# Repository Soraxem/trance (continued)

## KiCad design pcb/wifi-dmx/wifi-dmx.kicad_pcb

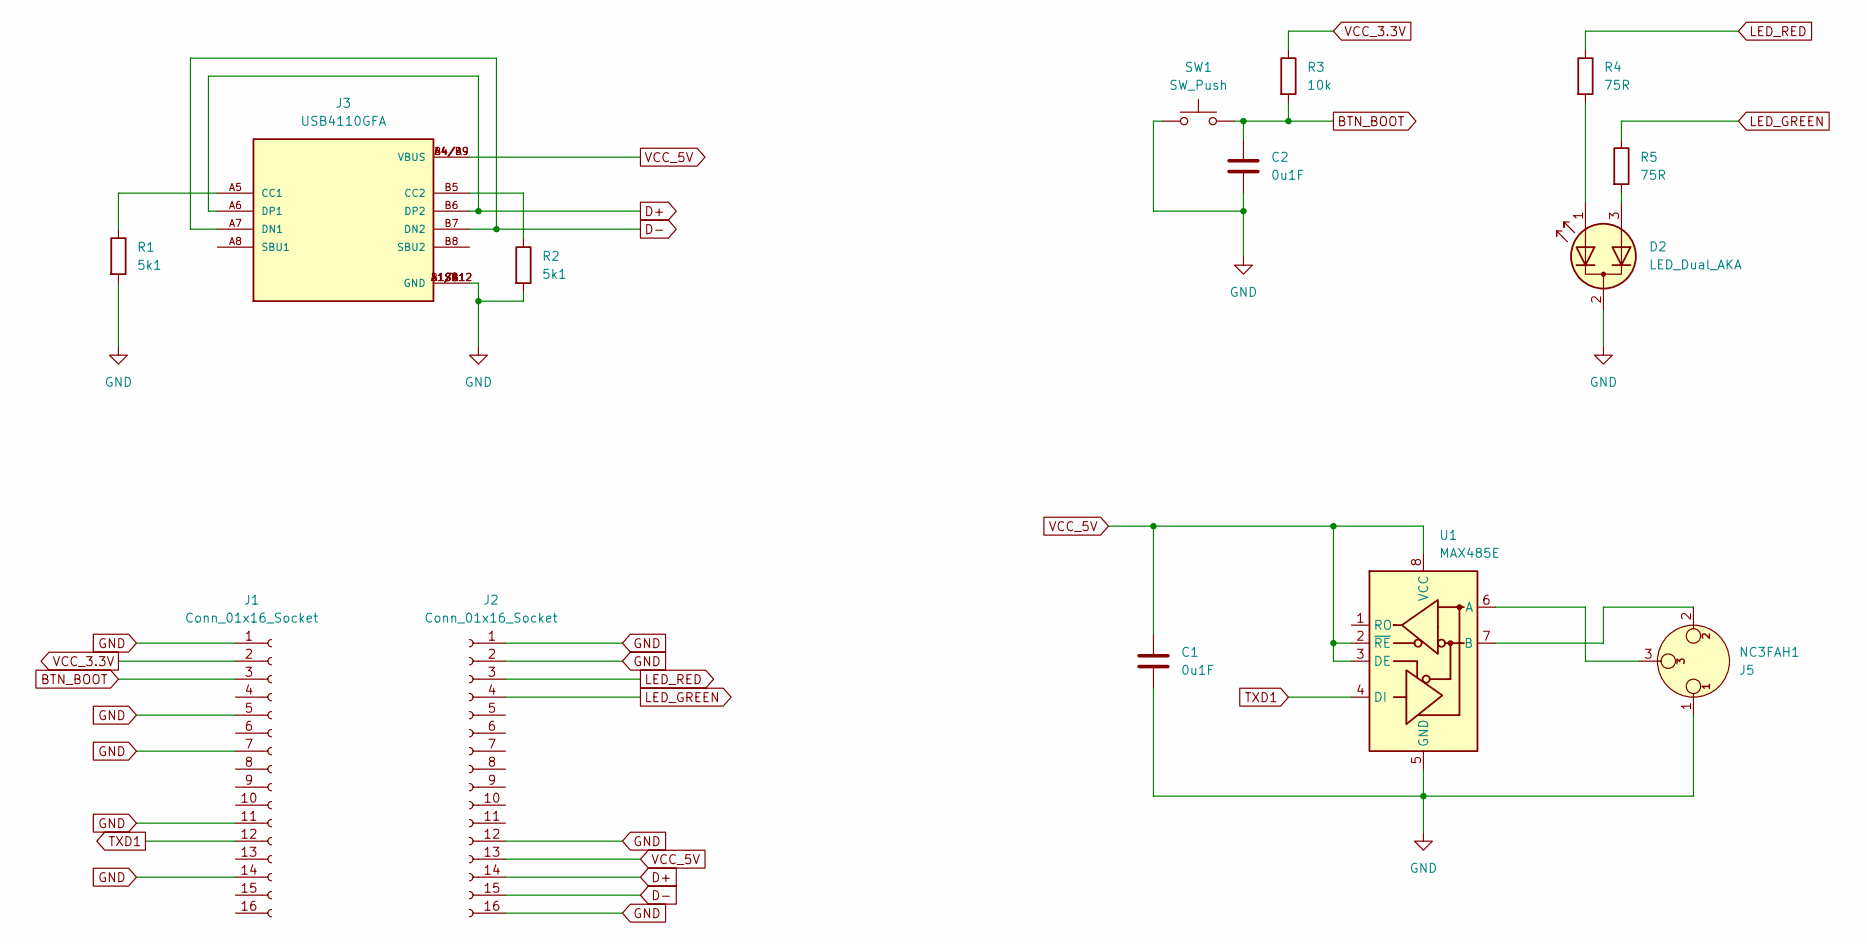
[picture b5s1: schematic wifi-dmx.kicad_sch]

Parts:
C1, C2: 0u1F; C_0402_1005Metric_Pad0.74x0.62mm_HandSolder; MOUSER_PART_NUMBER 187-CL05F104ZO5NNND
D2: LED_Dual_AKA; LED_D5.0mm-3_Horizontal_O3.81mm_Z3.0mm
J1, J2: Conn_01x16_Socket; PinHeader_1x16_P2.54mm_Vertical; MOUSER_PART_NUMBER 200-SSW11601TS
J3: USB4110GFA; GCT_USB4110GFA; MOUSER_PART_NUMBER 640-USB4110-GF-A; DigiKey_Part_Number 2073-USB4110-GF-A-2-ND
J5: NC3FAH1; Jack_XLR_Neutrik_NC3FAH1_Horizontal
R1, R2: 5k1; R_0402_1005Metric_Pad0.72x0.64mm_HandSolder; MOUSER_PART_NUMBER 71-CRCW0402-5.1K-E3
R3: 10k; R_0402_1005Metric_Pad0.72x0.64mm_HandSolder; MOUSER_PART_NUMBER 71-CRCW0402-10K-E3
R4, R5: 75R; R_0402_1005Metric_Pad0.72x0.64mm_HandSolder; MOUSER_PART_NUMBER 71-CRCW040275R0JNEDC
SW1: SW_Push; SW_Tactile_SPST_Angled_PTS645Vx58-2LFS
U1: MAX485E; SOIC-8_3.9x4.9mm_P1.27mm

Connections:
BTN_BOOT: C2.1, J1.3, R3.2, SW1.2
D+: J2.14, J3.A6 (DP1), J3.B6 (DP2)
D-: J2.15, J3.A7 (DN1), J3.B7 (DN2)
GND: C1.2, C2.2, D2.2 (K), J1.1, J1.5, J1.7, J1.11, J1.14, J2.1, J2.2, J2.12, J2.16, J3.A1/B12 (GND), J3.B1/A12 (GND), J3.S1 (GND), J3.S2 (GND), J3.S3 (GND), J3.S4 (GND), J5.1, R1.2, R2.2, SW1.1, U1.5 (GND)
LED_GREEN: J2.4, R5.1
LED_RED: J2.3, R4.1
unnamed: D2.1 (A1), R4.2
unnamed: D2.3 (A2), R5.2
unnamed: J3.A5 (CC1), R1.1
unnamed: J3.B5 (CC2), R2.1
unnamed: J5.3, U1.6 (A)
unnamed: J5.2, U1.7 (B)
TXD1: J1.12, U1.4 (DI)
VCC_3.3V: J1.2, R3.1
VCC_5V: C1.1, J2.13, J3.A4/B9 (VBUS), J3.B4/A9 (VBUS), U1.2 (~RE), U1.3 (DE), U1.8 (VCC)

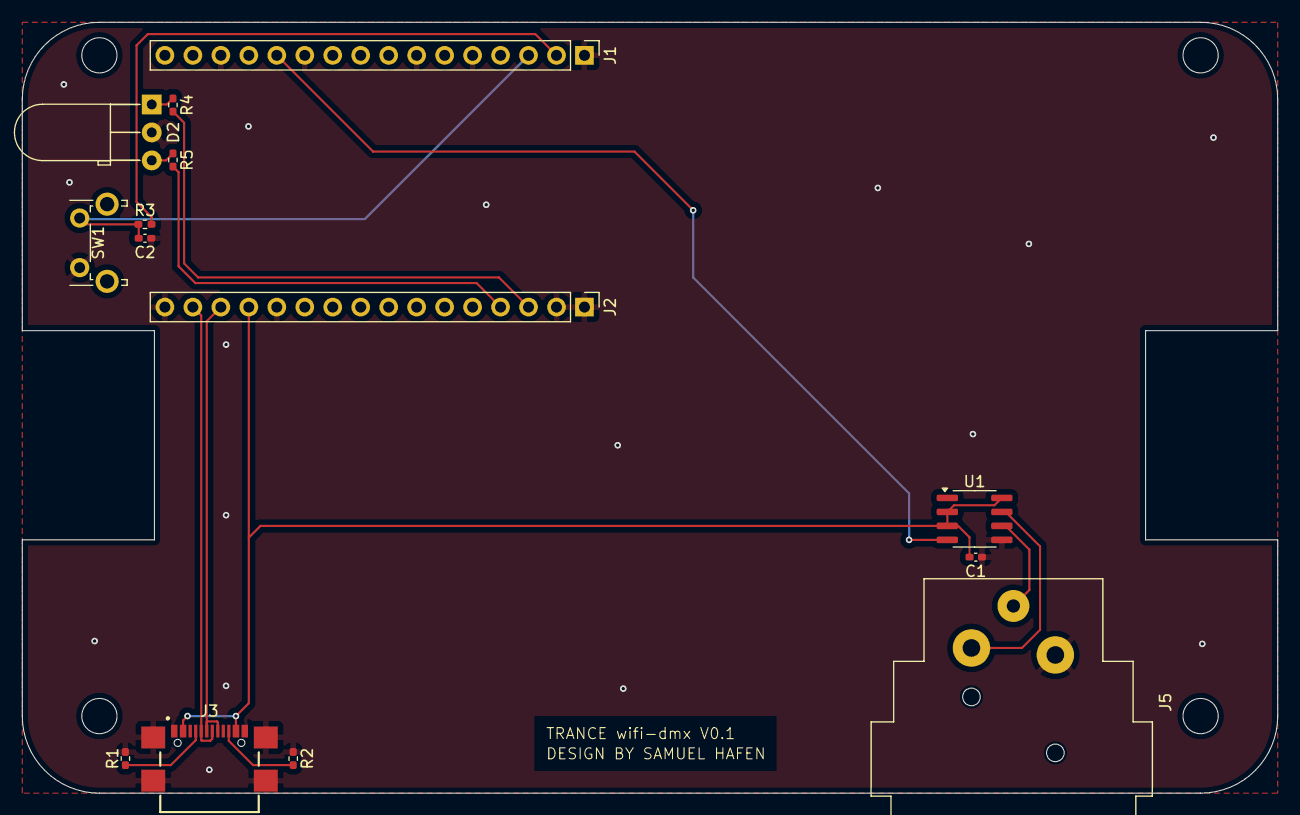
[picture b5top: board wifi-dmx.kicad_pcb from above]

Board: 2 copper layers, 114.0 x 70.0 mm, 14 parts (0 on the bottom side), 15 nets.

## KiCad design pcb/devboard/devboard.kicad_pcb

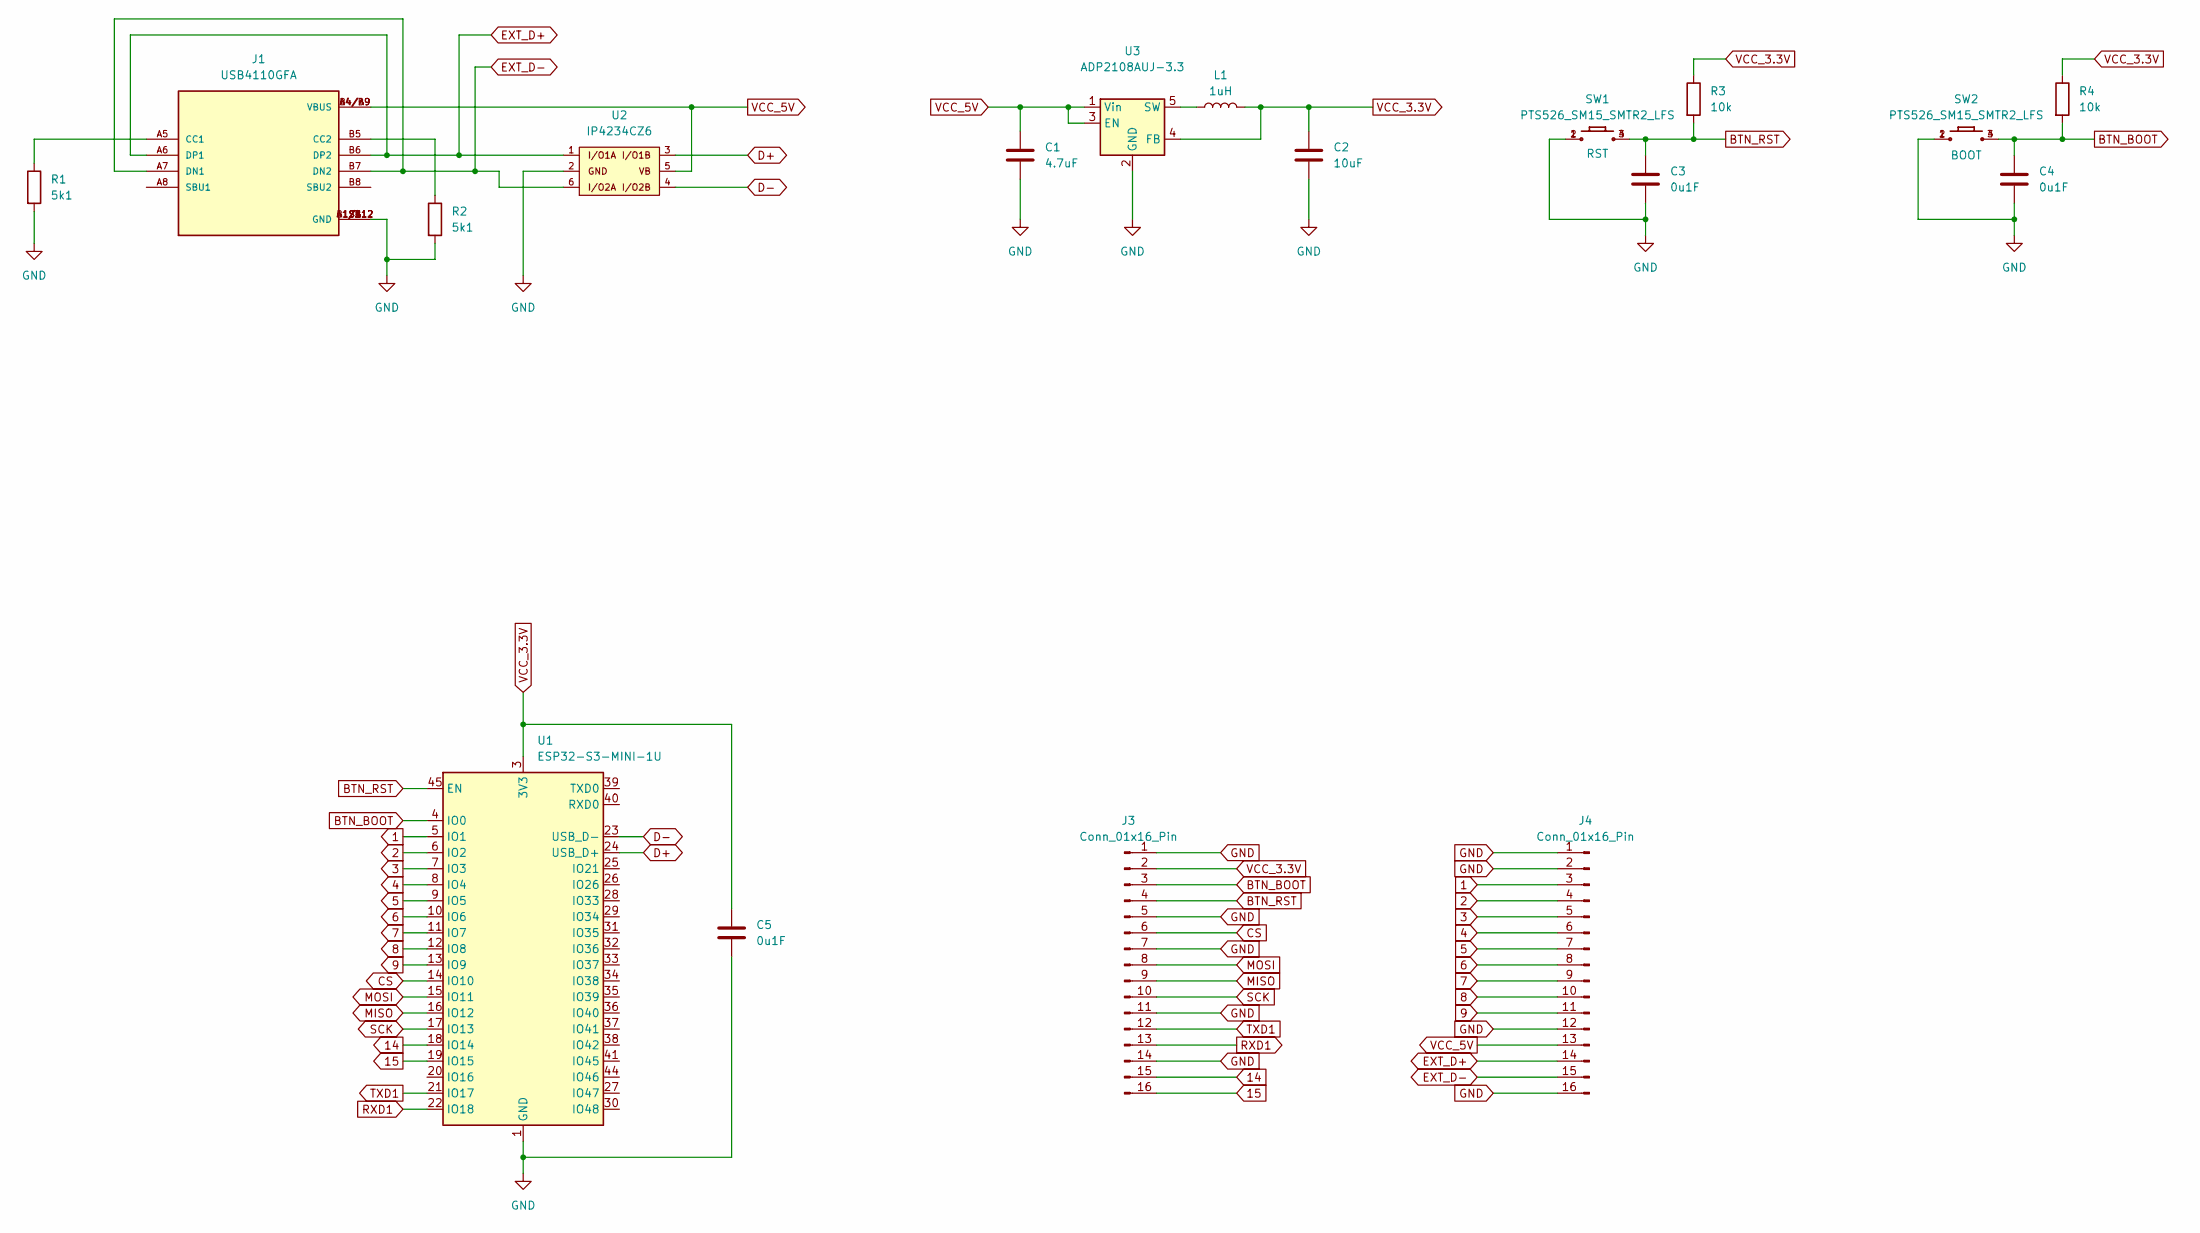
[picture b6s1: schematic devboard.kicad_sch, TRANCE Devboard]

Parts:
C1: 4.7uF; C_0603_1608Metric; MOUSER_PART_NUMBER 187-CL10A475KO8NNNC
C2: 10uF; C_0805_2012Metric; MOUSER_PART_NUMBER 187-CL21A106KOQNNNF
C3, C4, C5: 0u1F; C_0402_1005Metric; MOUSER_PART_NUMBER 187-CL05F104ZO5NNND
J1: USB4110GFA; GCT_USB4110GFA; MOUSER_PART_NUMBER 640-USB4110-GF-A; DigiKey_Part_Number 2073-USB4110-GF-A-2-ND
J3, J4: Conn_01x16_Pin; PinHeader_1x16_P2.54mm_Vertical; MOUSER_PART_NUMBER 200-TSW11607TS
L1: 1uH; L_0805_2012Metric; MOUSER_PART_NUMBER 81-LQM21PN1R0MC0D
R1, R2: 5k1; R_0402_1005Metric; MOUSER_PART_NUMBER 71-CRCW0402-5.1K-E3
R3, R4: 10k; R_0402_1005Metric; MOUSER_PART_NUMBER 71-CRCW0402-10K-E3
SW1, SW2: PTS526_SM15_SMTR2_LFS; PTS526SM15SMTR2LFS; MOUSER_PART_NUMBER 611-PTS526SM15SMTR2L
U1: ESP32-S3-MINI-1U; ESP32-S2-MINI-1U; MOUSER_PART_NUMBER 356-ESP32S3MINI1UN8
U2: IP4234CZ6; IP4234CZ6_SOT-457-6; MOUSER_PART_NUMBER 771-IP4234CZ6
U3: ADP2108AUJ-3.3; TSOT-23-5; MOUSER_PART_NUMBER 584-ADP2108AUJZ3.3R7

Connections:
1: J4.3, U1.5 (IO1)
2: J4.4, U1.6 (IO2)
3: J4.5, U1.7 (IO3)
4: J4.6, U1.8 (IO4)
5: J4.7, U1.9 (IO5)
6: J4.8, U1.10 (IO6)
7: J4.9, U1.11 (IO7)
8: J4.10, U1.12 (IO8)
9: J4.11, U1.13 (IO9)
14: J3.15, U1.18 (IO14)
15: J3.16, U1.19 (IO15)
BTN_BOOT: C4.1, J3.3, R4.2, SW2.3, SW2.4, U1.4 (IO0)
BTN_RST: C3.1, J3.4, R3.2, SW1.3, SW1.4, U1.45 (EN)
CS: J3.6, U1.14 (IO10)
D+: U1.24 (USB_D+), U2.3
D-: U1.23 (USB_D-), U2.4
EXT_D+: J1.A6 (DP1), J1.B6 (DP2), J4.14, U2.1
EXT_D-: J1.A7 (DN1), J1.B7 (DN2), J4.15, U2.6
GND: C1.2, C2.2, C3.2, C4.2, C5.2, J1.A1/B12 (GND), J1.B1/A12 (GND), J1.S1 (GND), J1.S2 (GND), J1.S3 (GND), J1.S4 (GND), J3.1, J3.5, J3.7, J3.11, J3.14, J4.1, J4.2, J4.12, J4.16, R1.2, R2.2, SW1.1, SW1.2, SW2.1, SW2.2, U1.1 (GND), U1.2 (GND), U1.42 (GND), U1.43 (GND), U1.46 (GND), U1.47 (GND), U1.48 (GND), U1.49 (GND), U1.50 (GND), U1.51 (GND), U1.52 (GND), U1.53 (GND), U1.54 (GND), U1.55 (GND), U1.56 (GND), U1.57 (GND), U1.58 (GND), U1.59 (GND), U1.60 (GND), U1.61 (GND), U1.62 (GND), U1.63 (GND), U1.64 (GND), U1.65 (GND), U2.2, U3.2 (GND)
MISO: J3.9, U1.16 (IO12)
MOSI: J3.8, U1.15 (IO11)
unnamed: J1.A5 (CC1), R1.1
unnamed: J1.B5 (CC2), R2.1
unnamed: L1.1, U3.5 (SW)
RXD1: J3.13, U1.22 (IO18)
SCK: J3.10, U1.17 (IO13)
TXD1: J3.12, U1.21 (IO17)
VCC_3.3V: C2.1, C5.1, J3.2, L1.2, R3.1, R4.1, U1.3 (3V3), U3.4 (FB)
VCC_5V: C1.1, J1.A4/B9 (VBUS), J1.B4/A9 (VBUS), J4.13, U2.5, U3.1 (Vin), U3.3 (EN)

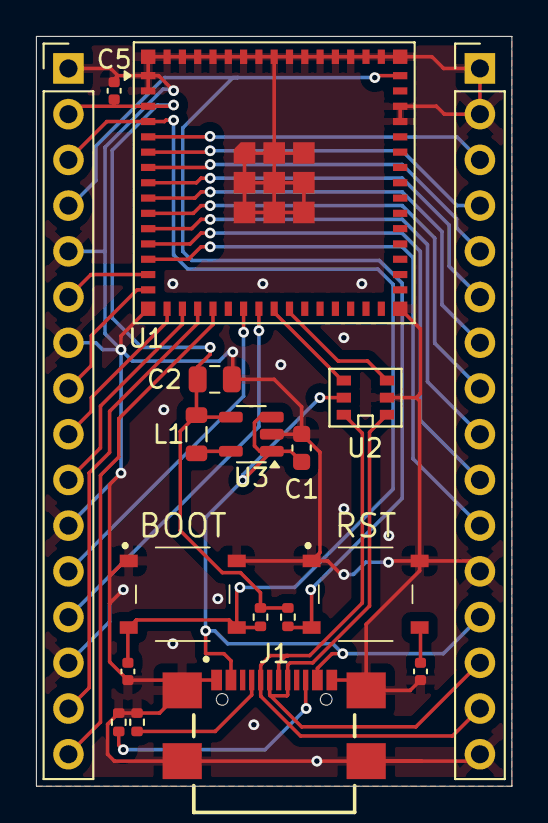
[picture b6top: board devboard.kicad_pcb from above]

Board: 2 copper layers, 26.4 x 41.7 mm, 18 parts (0 on the bottom side), 29 nets.

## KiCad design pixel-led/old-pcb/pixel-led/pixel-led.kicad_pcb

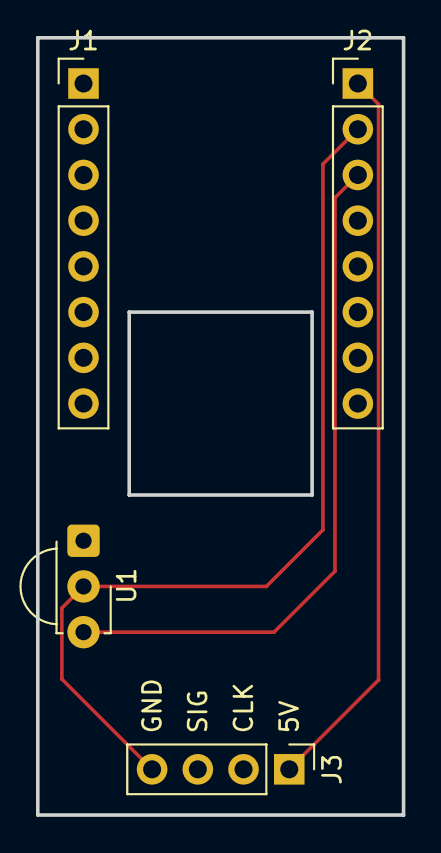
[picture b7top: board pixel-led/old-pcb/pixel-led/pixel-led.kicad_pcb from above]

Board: 2 copper layers, 20.3 x 43.2 mm, 4 parts (0 on the bottom side), 3 nets.

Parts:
J1, J2: Conn_01x08_Socket; PinHeader_1x08_P2.54mm_Vertical
J3: Conn_01x04_Socket; PinHeader_1x04_P2.54mm_Vertical
U1: TL1838; Vishay_MINICAST-3Pin

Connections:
3V3: J2.3, U1.3 (Vs)
5V5: J2.1, J3.1
GND: J2.2, J3.4, U1.2 (GND)

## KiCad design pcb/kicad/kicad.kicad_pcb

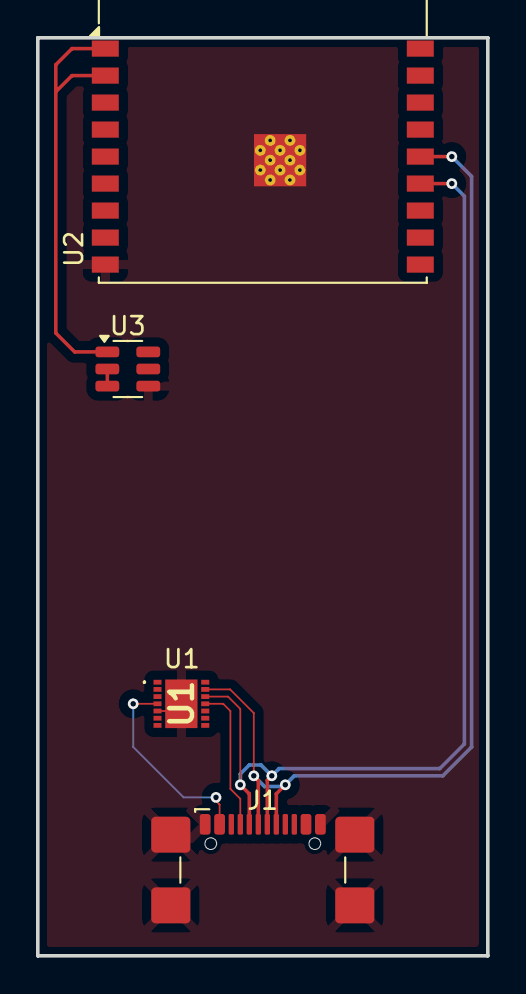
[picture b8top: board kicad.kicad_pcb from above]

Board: 2 copper layers, 25.0 x 51.0 mm, 4 parts (0 on the bottom side), 8 nets.

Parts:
J1: USB_C_Receptacle_USB2.0_16P; USB_C_Receptacle_GCT_USB4110
U1: AP33771C; AP33771CFBZ13FA01
U2: ESP32-C3-WROOM-02
U3: AP63203WU; TSOT-23-6

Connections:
D+: J1.A6 (D+), J1.B6 (D+), U1.13 (DP), U2.14 (IO19)
D-: J1.A7 (D-), J1.B7 (D-), U1.12 (DN), U2.13 (IO18)
GND: J1.A1 (GND), J1.A12 (GND), J1.B1 (GND), J1.B12 (GND), J1.S1 (SHIELD), U1.5 (GND), U1.15, U2.9 (GND), U2.19 (GND), U3.4 (GND)
unnamed: J1.A5 (CC1), U1.11 (CC1)
unnamed: J1.B5 (CC2), U1.10 (CC2)
unnamed: J1.A4 (VBUS), J1.A9 (VBUS), J1.B4 (VBUS), J1.B9 (VBUS), U1.4 (ISENP)
unnamed: U2.1 (3V3), U2.2 (EN), U3.1 (FB)
PWR: U3.2 (EN), U3.3 (IN)

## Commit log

2024-01-23 Created Project
    Created Project in LibrePCB
2024-01-23 Created first draft
    Created a first draft of the circuit and board.
2025-02-15 creating concepts and prototypes
2025-02-15 adding enclosure prototype
2025-02-15 ignoring Freecad Backup files
2025-02-15 removing angle from plug
2025-04-23 creating custom devboard
2025-04-23 connecting all remaining IOs
2025-04-23 adding mouser part number to all parts
2025-04-24 designed pcb
2025-04-29 changing pinout to more gnd
2025-05-03 removing old approaches
2025-05-03 changing license to CC0
2025-05-03 adding Kicad gitignore entrys
2025-05-03 adding a new pcb, on which de devboard will be used.
2025-05-27 adding GND vias, creating gerber files
2025-05-28 adding XLD connector
2025-05-29 adding pdf of schematic and pcb
2025-05-29 adding measurements to pcb
2025-05-29 finishing schematic and organizing pcb
2025-05-29 removing wall adapter enclosure
2025-05-29 adding project for eth-dmx configuration
2025-05-30 adding enclosure sketch
2025-06-02 creating enclosure design
2025-06-03 adding lid
2025-06-03 adding button and led to pcb
2025-06-04 finishing schematic, finishing pcb, integrating pcb-stl with enclosure
2025-06-04 adding button and led to enclosure
2025-06-04 adding board details on silkscreen
2025-06-04 adding mouser part numbers
2025-06-04 hiding mouser part numbers in schematic
2025-06-07 adding SMA hole
2025-06-07 adding clip mount
2025-07-02 creating schematic for eurolite led 7c-7 retrofit
2025-07-02 adding current project status
2025-07-02 adding cover
2025-07-02 creating schematic for usb-dmx
2025-07-03 creating pcb for usb-dmx
2025-07-03 introducing patched together firmware
2025-07-08 adding receiving voltage divider and renaming components
2025-07-14 preparing usb-dmx for production
2025-07-14 removing modding attempt
2025-07-14 reorganizing repo, removing stale projects
2025-07-14 adding Webinterface layout file
2025-07-14 adding external antenna to schematic
2025-07-14 finishing preliminary webinterface layout
2025-07-15 adding more style to webinterface
2025-07-15 adding new firmware, adding wifi concept
2025-07-15 adding network preferences loading
2025-07-15 adding web and dns server for captive portal
2025-07-16 setting up webinterface and templating
2025-08-13 Adding other Voltage Regulator
2025-08-27 generalizing firmware
2025-08-29 Remove color codes from errors
2025-08-29 adding wifi configuration macros
2025-08-29 refactoring main code
2025-08-29 adding new device
2025-09-06 fixing pcb, reorganizing firmware library
2025-09-30 updating gerber files
2025-09-30 adding usb-dmx firmware
2025-10-02 adding dmx output, removing pwm outputs
2025-10-03 cleaning up repository
2025-10-03 adding larger capacitor to esp and exchanging parts
2025-10-06 fingind aliexpress alternatives
2025-10-07 creating pcb layout
2025-12-16 adding a new license
2025-12-17 updating usb-dmx-firmware
2025-12-19 adding DMX startcode
2025-12-21 designing-housing
2025-12-22 changing to 2 part housing
2025-12-22 creating rough design
2025-12-22 updating documentation
2025-12-23 adding cutouts for USB-A shield connectors
2026-01-12 moved sketch, used usb-dmx as template
2026-01-12 layouting
2026-01-13 finishing layout
2026-01-19 updating readme
2026-01-19 adding links to readme
2026-01-21 creating gerber
2026-01-22 adding ir-remote for led-strip
2026-01-22 moving firmware with ir-remote, adding palette
2026-01-22 reworking animation system, for smooth speed change
2026-02-07 changing data Pin
2026-02-09 moving usb-a-plug, changing esp32-partnumber
2026-02-09 adding documentation for usb-dmx
